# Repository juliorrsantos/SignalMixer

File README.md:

# Misturador de sinais

## Circuito desenvolvido como complemento para estudos de FFT
O diagrama esquemático do circuito pode ser conferido **[aqui](./KiCad/SignalMixer/SignalMixer.pdf).**

Características:
- Duas entradas de sinais analógicos, com opção de alta impedância de entrada ou 50 ohms.
- configuração de ganho por canal de 1x, 10x, 100X e valores intermediarios pela combinação dos resistores.
- Alimentação por fonte simples de 24Vcc.
- A saída será o resultado da soma dos dois sinais de entrada, multiplicado por seus respectivos ganhos.

obs.: A fonte utilizada para alimentação do circuito não deverá ser a mesma que alimenta o gerador de sinais da entrada, ou o circuito conectado à saída.

## Imagens da placa

### Vista frontal

### Vista traseira

## Simulação

Simulação do circuito no LTspice com a injeção de duas senoides, em 60 e 1200Hz respectivamente. Ambas com tensão de pico de 1V.

É possível notar a soma dos dois sinais no terceiro gráfico, comprovando o funcionamento do circuito.

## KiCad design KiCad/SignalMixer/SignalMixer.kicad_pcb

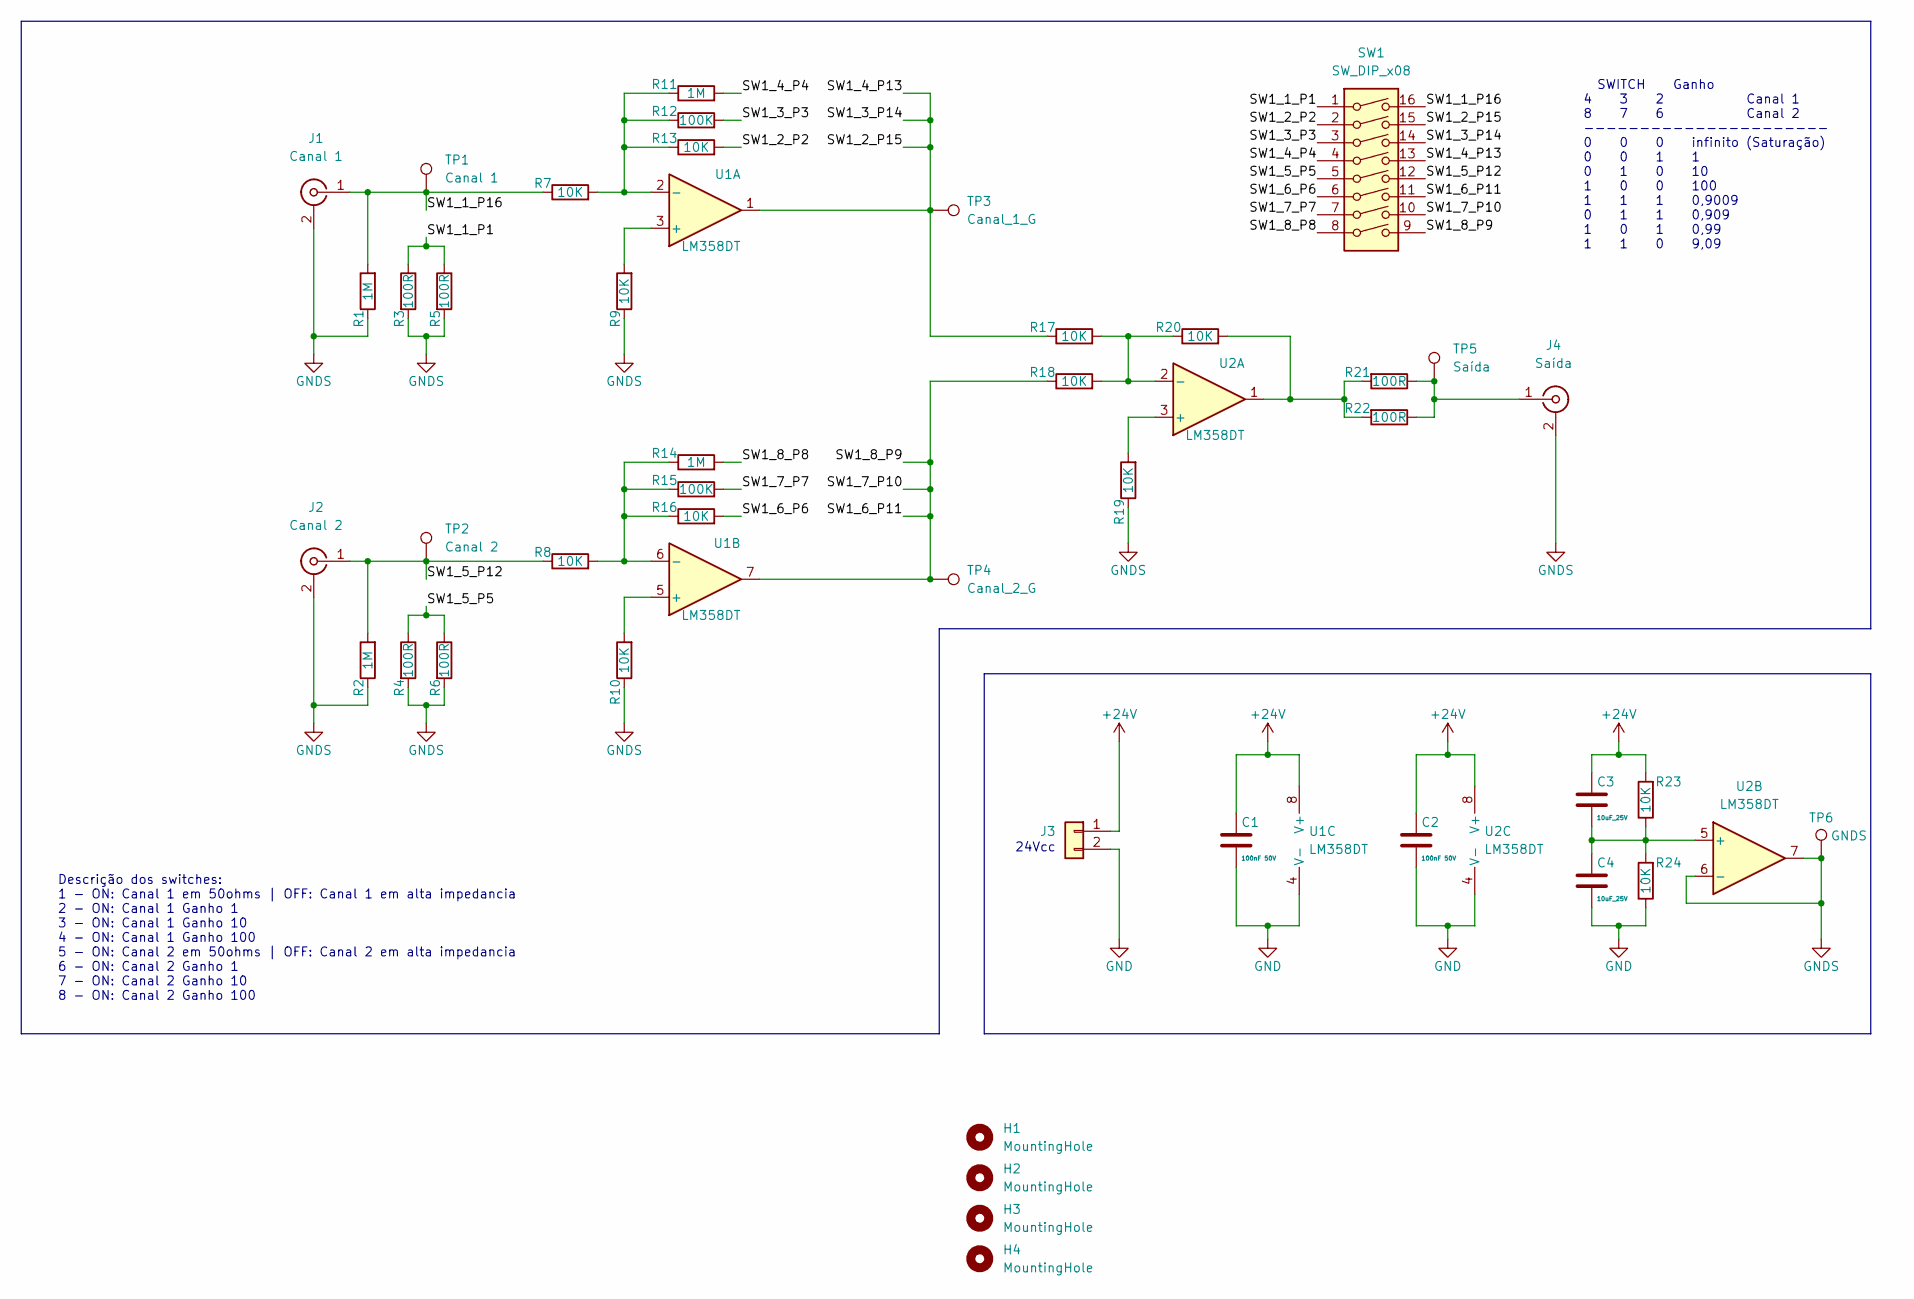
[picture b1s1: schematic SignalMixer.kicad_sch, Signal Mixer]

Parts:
C1, C2: 100nF 50V; C_0603_1608Metric; LCSC C1591
C3, C4: 10uF_25V; C_0603_1608Metric; LCSC C96446
H1, H2, H3, H4: MountingHole; MountingHole_3.2mm_M3
J1: Canal 1; BNC_DOSIN-801-0083
J2: Canal 2; BNC_DOSIN-801-0083
J3: Conn_01x02; JST_XH_B02B-XH-A_02x2.50mm_Straight
J4: Saída; BNC_DOSIN-801-0083
R1, R2, R11, R14: 1M; R_0603_1608Metric; LCSC C22935
R3, R4, R5, R6, R21, R22: 100R; R_0805_2012Metric; LCSC C17408
R7, R8, R9, R10, R13, R16, R17, R18, R19, R20, R23, R24: 10K; R_0603_1608Metric; LCSC C25804
R12, R15: 100K; R_0603_1608Metric; LCSC C25803
SW1: SW_DIP_x08; SW_DIP_SPSTx08_Slide_9.78x22.5mm_W7.62mm_P2.54mm
TP1: Canal 1; TestPoint_RH-5000; LCSC C5277086
TP2: Canal 2; TestPoint_RH-5000; LCSC C5277086
TP3: Canal_1_G; TestPoint_RH-5000; LCSC C5277086
TP4: Canal_2_G; TestPoint_RH-5000; LCSC C5277086
TP5: Saída; TestPoint_RH-5000; LCSC C5277086
TP6: GNDS; TestPoint_RH-5000; LCSC C5277086
U1, U2: LM358DT; SOIC-8_3.9x4.9mm_P1.27mm; LCSC C9418

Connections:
+24V: C1.1, C2.1, C3.1, J3.1, R23.2, U1.8 (V+), U2.8 (V+)
/SW1_1_P1: R3.1, R5.1, SW1.1
/SW1_1_P16: J1.1 (In), R1.2, R7.1, SW1.16, TP1.1
/SW1_2_P2: R13.2, SW1.2
/SW1_2_P15: R17.1, SW1.13, SW1.14, SW1.15, TP3.1, U1.1
/SW1_3_P3: R12.2, SW1.3
/SW1_4_P4: R11.2, SW1.4
/SW1_5_P5: R4.1, R6.1, SW1.5
/SW1_5_P12: J2.1 (In), R2.2, R8.1, SW1.12, TP2.1
/SW1_6_P6: R16.2, SW1.6
/SW1_6_P11: R18.1, SW1.9, SW1.10, SW1.11, TP4.1, U1.7
/SW1_7_P7: R15.2, SW1.7
/SW1_8_P8: R14.2, SW1.8
GND: C1.2, C2.2, C4.2, J3.2, R24.1, U1.4 (V-), U2.4 (V-)
GNDS: J1.2 (Ext), J2.2 (Ext), J4.2 (Ext), R1.1, R2.1, R3.2, R4.2, R5.2, R6.2, R9.1, R10.1, R19.1, TP6.1, U2.6 (-), U2.7
unnamed: C3.2, C4.1, R23.1, R24.2, U2.5 (+)
unnamed: J4.1 (In), R21.1, R22.1, TP5.1
unnamed: R9.2, U1.3 (+)
unnamed: R10.2, U1.5 (+)
unnamed: R7.2, R11.1, R12.1, R13.1, U1.2 (-)
unnamed: R8.2, R14.1, R15.1, R16.1, U1.6 (-)
unnamed: R17.2, R18.2, R20.1, U2.2 (-)
unnamed: R19.2, U2.3 (+)
unnamed: R20.2, R21.2, R22.2, U2.1

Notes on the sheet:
24Vcc
Descrição dos switches: 1 - ON: Canal 1 em 50ohms | OFF: Canal 1 em alta impedancia 2 - ON: Canal 1 Ganho 1 3 - ON: Canal 1 Ganho 10 4 - ON: Canal 1 Ganho 100 5 - ON: Canal 2 em 50ohms | OFF: Canal 2 em alta impedancia 6 - ON: Canal 2 Ganho 1 7 - ON: Canal 2 Ganho 10 8 - ON: Canal 2 Ganho 100
SWITCH Ganho 4 3 2 Canal 1 8 7 6 Canal 2 ---------------------- 0 0 0 infinito (Saturação) 0 0 1 1 0 1 0 10 1 0 0 100 1 1 1 0,9009 0 1 1 0,909 1 0 1 0,99 1 1 0 9,09

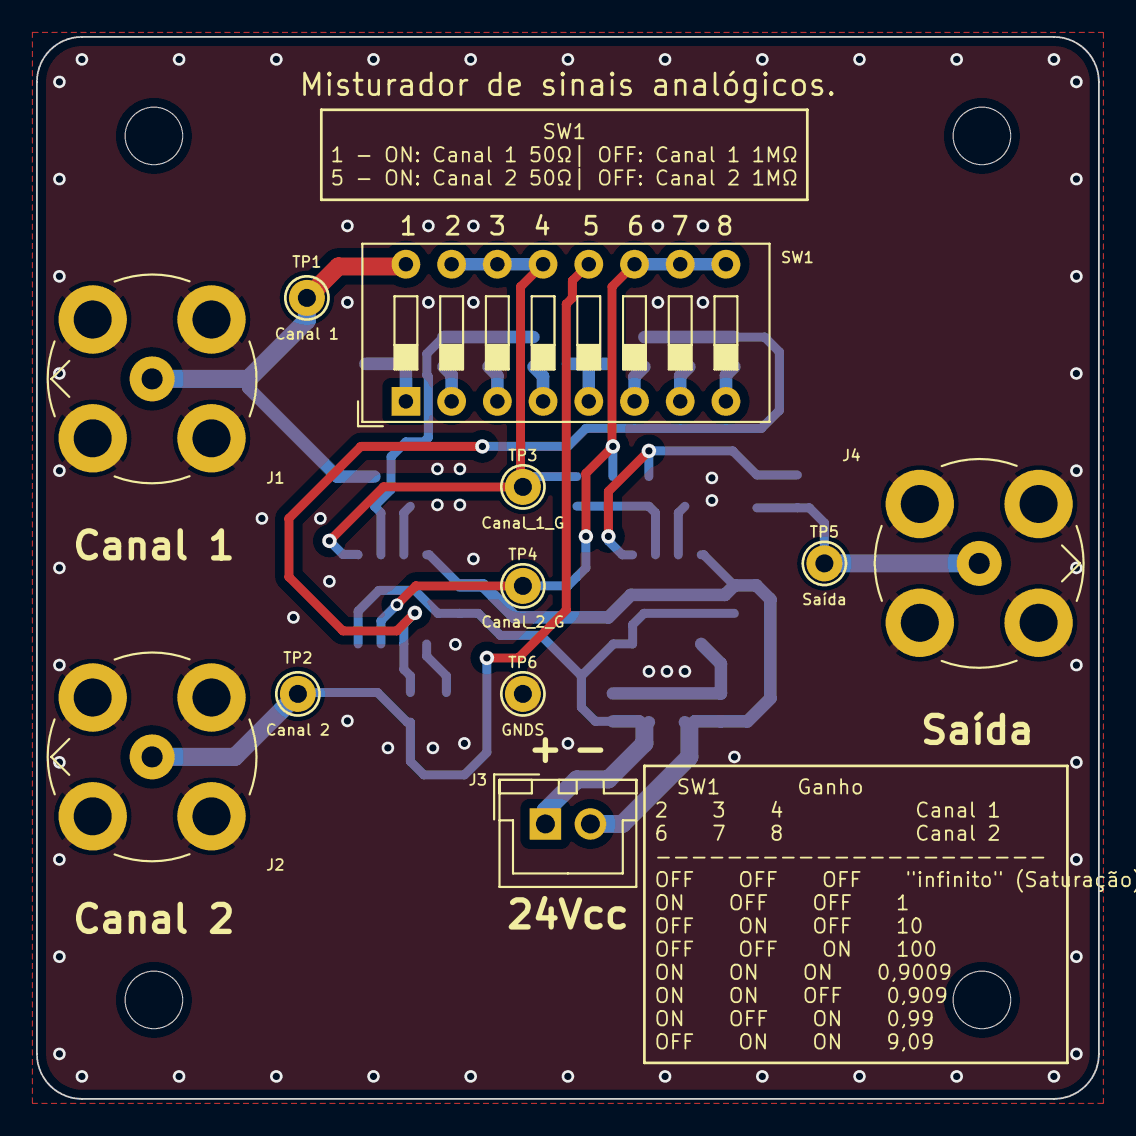
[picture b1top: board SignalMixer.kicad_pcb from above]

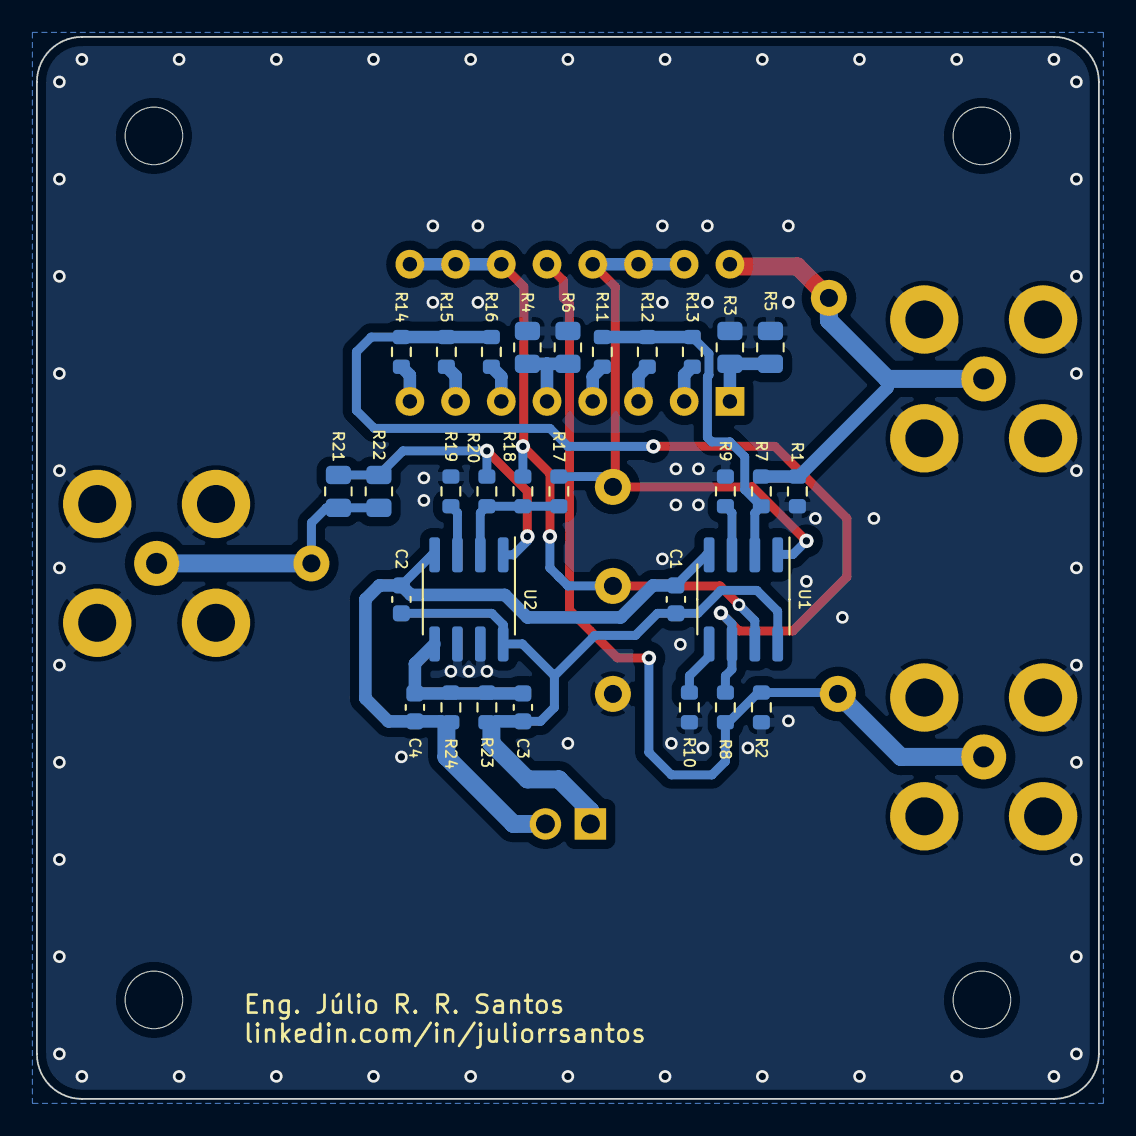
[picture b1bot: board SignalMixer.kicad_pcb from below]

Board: 2 copper layers, 59.0 x 59.0 mm, 45 parts (30 on the bottom side), 24 nets.

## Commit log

2024-01-28 criacao do readme
2024-01-28 Definição inicial das características do circuito
2024-01-28 Atualização nas características de projeto.
2024-01-28 Criacao do diagrama esquematico.
2024-01-29 Finalização do diagrama esquematico e geração do diagrama em PDF.
2024-01-29 Atualizacao do readme.
2024-01-29 Adicionado resistor de 1M nas entradas para evitar flutuacao quando o resistor de 50 ohms for desconectado.
2024-02-01 Definicao dos footprints, atualizacao do esquematico e inicio do roteamento da pcb.
2024-02-08 Finalizacao do layout da PCB.
2024-02-08 Inclusao de imagens no Readme.
2024-02-08 Inclusao do link do diagrama no readme.
2024-02-09 Inclusao da simulacao em LTspice
